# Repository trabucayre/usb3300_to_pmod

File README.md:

# Waveshare USB3300 to dual PMOD PCB adapter

This repository is dedicated to a PCB adapter for the
[Waveshare USB3300 USB HS Board](https://www.waveshare.com/wiki/USB3300_USB_HS_Board).

The Waveshare module exposes the **USB3300 ULPI** interface on a 2x10 2.54 mm
header. Wiring this header to an FPGA board with loose jumpers can easily cause
signal integrity issues, especially with the 60 MHz `CLKOUT` signal and the
8-bit ULPI data bus.

This adapter converts the Waveshare 2x10 header to two standard 2x6 PMOD-style
connectors:

- `J3` carries the 8-bit ULPI data bus.
- `J2` carries the ULPI control signals, clock and reset.
- `J4` is the 2x10 connector for the Waveshare USB3300 board.
- `J1` exposes `+5V` and `GND`.

The board is passive: it does not include level shifters, buffers or regulators.
The FPGA board must be compatible with 3.3 V I/O for the ULPI signals.

<center></center>

## Connector mapping

The PMOD connectors are dual-row 2x6 headers. Pins `1` to `6` are on the first
row, and pins `7` to `12` are on the second row.

### PMOD J3: ULPI data bus

| Row 1 pin | Signal  | Row 2 pin | Signal  |
| --------- | ------- | --------- | ------- |
| 1         | `DATA6` |  7        | `DATA7` |
| 2         | `DATA4` |  8        | `DATA5` |
| 3         | `DATA2` |  9        | `DATA3` |
| 4         | `DATA0` | 10        | `DATA1` |
| 5         | `GND`   | 11        | `GND`   |
| 6         | `+3.3V` | 12        | `+3.3V` |

### PMOD J2: ULPI control

| Row 1 pin | Signal  | Row 2 pin |  Signal  |
| --------- | ------- | --------- | -------- |
| 1         | `STP`   |  7        | NC       |
| 2         | `NXT`   |  8        | NC       |
| 3         | NC      |  9        | `CLKOUT` |
| 4         | `DIR`   | 10        | `RESET`  |
| 5         | `GND`   | 11        | `GND`    |
| 6         | `+3.3V` | 12        | `+3.3V`  |

### Waveshare USB3300 header J4

| J4 pin | Signal   | J4 pin | Signal  |
| ------ | -------- | ------ | ------- |
|  1     | `+5V`    |  2     | `DATA0` |
|  3     | `+5V`    |  4     | `DATA1` |
|  5     | NC       |  6     | `DATA2` |
|  7     | `RESET`  |  8     | `DATA3` |
|  9     | `CLKOUT` | 10     | `DATA4` |
| 11     | `DIR`    | 12     | `DATA5` |
| 13     | `NXT`    | 14     | `DATA6` |
| 15     | `STP`    | 16     | `DATA7` |
| 17     | `GND`    | 18     | `GND`   |
| 19     | `+3.3V`  | 20     | `+3.3V` |

## Electrical notes

- The adapter routes the ULPI bus directly between the Waveshare board and the
  PMOD connectors.
- `+3.3V` is distributed to the PMOD power pins and to the Waveshare header.
- `+5V` is routed to the Waveshare header and to the auxiliary `J1` header (Only
  required in device mode).
- Use short PMOD connections and keep both PMOD connectors attached to the same
  FPGA bank when possible.
- Verify the target board pinout before connecting. Not all 2x6 connectors use
  the same PMOD orientation or power-pin placement.

## Examples

The `examples` directory contains modified LiteX targets using the USB3300 as a
USB CDC ACM UART.

### Prerequisites

Using CDC ACM requires [amaranth](https://github.com/amaranth-lang/amaranth),
[Luna](https://github.com/greatscottgadgets/luna) and
[LiteX](https://github.com/enjoy-digital/litex).

**amaranth**

```bash
git clone https://github.com/amaranth-lang/amaranth.git
cd amaranth
# v0.5.8 is required by Luna
git checkout v0.5.8
pip3 install --user --break-system-packages -e .
cd ..
```

**Luna**

```bash
git clone https://github.com/greatscottgadgets/luna.git
cd luna
git checkout 0.2.3
# A commit has introduced a regression and must be reverted
# (https://github.com/greatscottgadgets/luna/issues/280)
git revert --no-edit cf6abaae922bd3f04ca6118f0a7d26b768859d28
pip3 install --user --break-system-packages -e .
cd ..
```

**LiteX**

This step is well documented in the
[official page](https://github.com/enjoy-digital/litex/#quick-start-guide)

### Build

To build a gateware image, use:

```bash
cd examples
./board_name.py --uart-name usb_acm --build --load
```

Where `board_name.py` may be:

- `digilent_arty_s7.py`

- `sipeed_tang_mega_138k.py`

- `arrow_axe5000.py`
  Requires the [Ziggy Bridge MKR](https://github.com/steieio/ziggybridge-mkr)

## Contact

E-mail: Gwenhael Goavec-Merou <gwenhael.goavec-merou@trabucayre.com></br>
Copyright (C) <b>2026</b></br>

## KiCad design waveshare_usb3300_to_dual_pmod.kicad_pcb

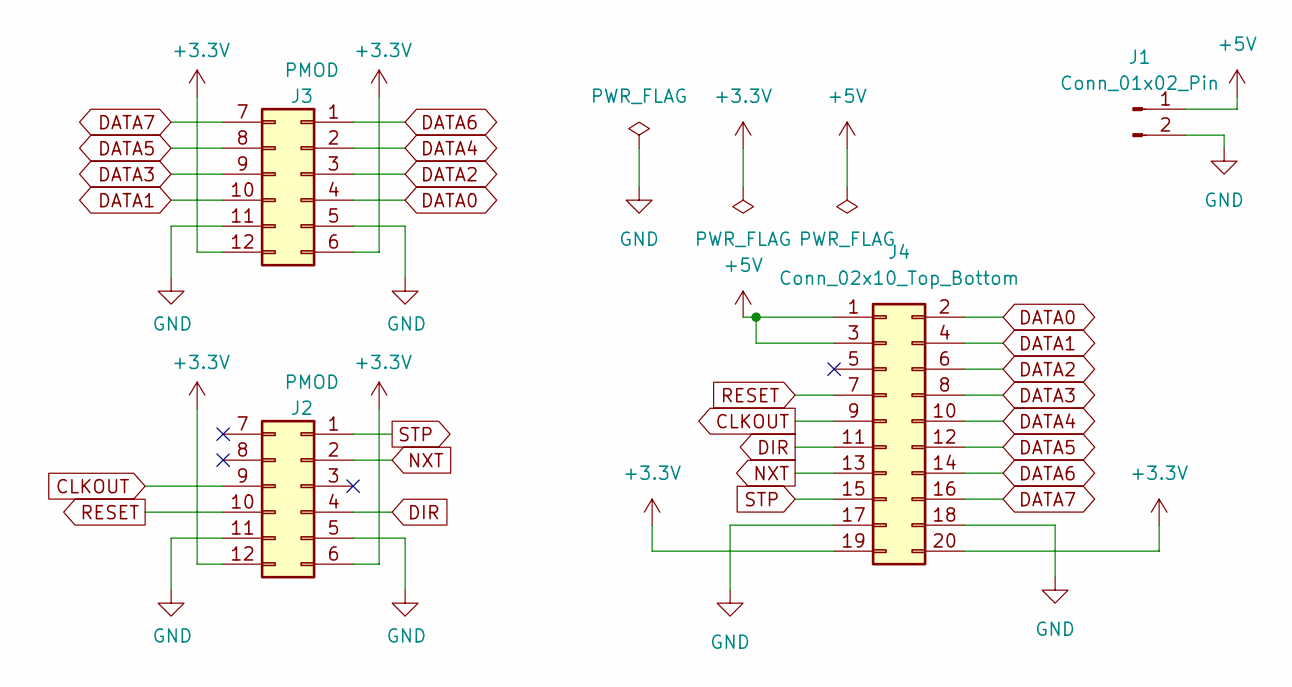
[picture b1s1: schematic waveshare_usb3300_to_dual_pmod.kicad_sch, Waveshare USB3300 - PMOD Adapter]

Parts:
J1: Conn_01x02_Pin; PinHeader_1x02_P2.54mm_Vertical
J2, J3: PMOD; PMODHeader_2x06_P2.54mm_Horizontal
J4: Conn_02x10_Top_Bottom; PinSocket_2x10_P2.54mm_Horizontal

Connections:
+3.3V: J2.6, J2.12, J3.6, J3.12, J4.19, J4.20
+5V: J1.1, J4.1, J4.3
CLKOUT: J2.9, J4.9
DATA0: J3.4, J4.2
DATA1: J3.10, J4.4
DATA2: J3.3, J4.6
DATA3: J3.9, J4.8
DATA4: J3.2, J4.10
DATA5: J3.8, J4.12
DATA6: J3.1, J4.14
DATA7: J3.7, J4.16
DIR: J2.4, J4.11
GND: J1.2, J2.5, J2.11, J3.5, J3.11, J4.17, J4.18
NXT: J2.2, J4.13
RESET: J2.10, J4.7
STP: J2.1, J4.15

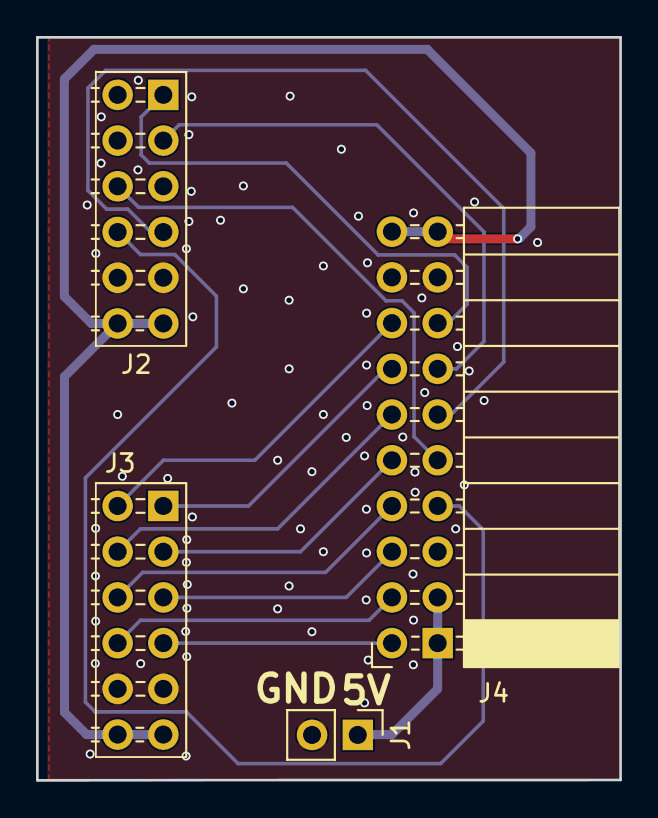
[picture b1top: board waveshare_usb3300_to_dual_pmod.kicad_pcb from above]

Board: 2 copper layers, 32.4 x 41.3 mm, 4 parts (0 on the bottom side), 16 nets.

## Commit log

2026-04-27 import kicad project
2026-04-27 examples: added AXE5000, Arty S7 and Tang Mega 138k targets with usb support
2026-04-27 lib/pkl/pinsocket_2.54mm_horizontal: custom J4/usb3300 footprint
2026-04-27 waveshare_usb3300_to_dual_pmod: changed j4 footprint, resize PCB
2026-04-27 README.md: added details
2026-04-27 picts: added some pictures
2026-04-28 README.md: improved with prerequisites section
2026-05-05 waveshare_usb3300_to_dual_pmod.kicad_pcb: reworks GND (thanks Goran!)
2026-05-07 waveshare_usb3300_to_dual_pmod.kicad_pcb: updates clock routing (thanks Goran)

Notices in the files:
waveshare_usb3300_to_dual_pmod.kicad_pcb:
License: CC-BY-SA 4.0
